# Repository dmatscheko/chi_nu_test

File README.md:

# χ_ν coherent-matter lift test

A pre-registered, falsifiable test of the OPH **χ_ν "coherent-matter lift"** claim
(the mechanism behind the OPH hoverboard concept), together with the audit work
that maps what the OPH corpus actually proves. The aim is to fix exactly what the
theory predicts **before** any data is taken, build the minimal self-reading device
the prediction requires, and let a pre-agreed decision rule, not either side's
prior, settle the outcome (detect / null / mundane / undefined).

Path shortcuts used throughout (`OPH:/`, `HOVER:/`, `ANS:/`) are defined in
Document A; `ANS:/` points at this repo's own [`communication/`](communication/)
directory.

## Layout

| Directory | What lives there |
|---|---|
| [`OPH_PROOF_CHAIN_HOLES.md`](OPH_PROOF_CHAIN_HOLES.md) | **The adversarial audit companion, two passes**: an independent hole inventory of the chain's interpretation layer (first pass F1–F19 against v5; second pass F20–F29 + per-finding disposition audits against v6.1; both passes independently *confirm* the formal layer by environment-level axiom sweeps). v6.1 adopted the first pass; **v7 closed both passes' mathematics by theorem** (T27/T28/T29 + F20/F25/F26 closures) and swept the second pass's residue ledger; disposition tables in the proof chain's §11. |
| [`OPH_PROOF_CHAIN_PAPER.md`](OPH_PROOF_CHAIN_PAPER.md) | **The expository paper**: the whole machine-checked proof chain written as ordinary mathematics: statement, proof, "why", and a plain-language paragraph per result. Adds nothing to the Lean tree (the tree is the authority); exists so a physicist can read the chain end-to-end without opening a `.lean` file. |
| [`test/`](test/) | **The physics test**: the pre-registration ledgers that govern the experiment. |
| [`proof_chain/`](proof_chain/) | **The minimal-proof-chain work**: what the OPH corpus proves (incl. the `formal/` Lean project that machine-checks it), the audit exchange with the OPH side, and the satellite-repo audits. |
| [`build/`](build/README.md) | **The hardware**: Milestone-1 self-reading piezo PoC (build plan, rev-2 electronics + schematics, jig, firmware) and the Stage-0 calibration results. |
| [`communication/`](communication/) | **The Q&A with the OPH side** (`ANS:/`): questions, replies, and the OPH-side PDFs. Absorbed from the former sibling repo on 2026-07-06. |

## The physics test (`test/`)

| File | Role |
|---|---|
| [`DOCUMENT_A_prediction_ledger.md`](test/DOCUMENT_A_prediction_ledger.md) | **Start here.** Imports the OPH math with verified provenance, records the agreed OPH-side inputs, discloses the conservation-law priors, and derives the falsifiable predictions + decision rule. Governs the outcome on its own. |
| [`DOCUMENT_C_run_matrix_and_error_budget.md`](test/DOCUMENT_C_run_matrix_and_error_budget.md) | The instrument, the run matrix (R-pre, ABBA, ACTIVE±/SHAM, blind controls), the error budget that fixes the detection floor, and the energy-budget logging. |
| [`DOCUMENT_B_critique_ledger.md`](test/DOCUMENT_B_critique_ledger.md) | Open-questions & credit ledger. Two live items, the ΔS-estimator bridge (G9) and the energy ledger (G10), plus the disposition of the original critique (mostly closed) and what stands regardless of any outcome. |

## The minimal proof chain (`proof_chain/`)

| File | Role |
|---|---|
| [`OPH_CORE_MINIMAL_PROOF_CHAIN.md`](proof_chain/OPH_CORE_MINIMAL_PROOF_CHAIN.md) | **v7.** The minimal proof chain for the core OPH idea: machine-checked (Lean) → paper-side theorems → conditional → asserted/calibrated, with the conservation-law bounds on the χ_ν chain. Background for all three ledgers. |
| [`formal/`](proof_chain/formal/) | **The Lean 4 project that machine-checks the chain**: 38 modules; 1284 non-internal theorem/def declarations swept at the environment level (v10 filter; earlier counts used a wider filter), 0 `sorry`, 0 custom axioms (incl. an attributed copy of the OPH core with its three `sorry`s discharged; the v7 modules closing the adversarial audit's mathematics; the v9 worldline/crawl theorems T36/T37; and the v10 campaign T38–T41: the parity splitting, two-power universality, the lone diagonal observer). See its [`README`](proof_chain/formal/README.md) and the statement-by-statement audit in [`RESULTS.md`](proof_chain/formal/RESULTS.md). |
| [`AUDIT_RESPONSE.md`](proof_chain/AUDIT_RESPONSE.md) | The OPH side's 2026-07-06 response to our audit: validity grading per gap + the July paper pass that answers it. |
| [`AUDIT_RESPONSE_REVIEW.md`](proof_chain/AUDIT_RESPONSE_REVIEW.md) | Our verification of that response: all pin-cites checked, the P-derivation code executed (two-P finding), three refinements (R1 feed-forward carrier, R2 falsifiers ≠ energy ledger, §P). |
| [`formal_audits/`](proof_chain/formal_audits/) | Raw audits of the `dula/` satellite repos (verdict: not proof-chain-relevant; one reusable artifact, ported). |

## How it fits together

**test/A**: what the theory predicts and how the result is decided ·
**test/C**: how it is measured · **test/B**: what stays open and what stands ·
**proof_chain/**: the standing of every imported claim and the audit exchange ·
**build/**: the device that produces the self-read receipt A requires ·
**communication/**: the primary-source Q&A the ledgers cite as `ANS:/`.

Version history lives in git: v0.1 ledgers (2026-06-02/03), the correction
pass ("corrections pass 1"), the v0.2 rewrite (2026-07-05), the audit exchange
and proof-chain v2 (2026-07-06), the v3/v4 `formal/` campaigns (the whole
chain machine-proven in one tree, 2026-07-06), the v5 campaign closing
the remaining open mathematics, incl. the D3 finite modular core and one
ledger erratum (2026-07-07), the v6 campaign settling the stride
conjecture (T25, the coprimality classification of two-column screens,
with the mirror lemma and the quotient lift as new tools) plus the
expository paper `OPH_PROOF_CHAIN_PAPER.md`, audited against the Lean tree,
and the v6.1 response to the adversarial audit `OPH_PROOF_CHAIN_HOLES.md`
(T26, the cosmological-constant step; the G10 pricing convention named;
the F18 erratum table applied; disposition in the proof chain's §11)
(2026-07-07), and the v7 campaign closing both audit passes' mathematics
by theorem (T27 Route A assembled; T28 the real-time modular flow; T29 the
channel bridge; the F20/F25/F26 closures; the ℤ₆ group isomorphism; the
theorem-grade energy anchors; the F22 evidence artifacts; the F21 residue
sweep) (2026-07-07). The former
`communication/` sibling repo's own history is at
https://github.com/dmatscheko/hoverboard-experimental-precursor.

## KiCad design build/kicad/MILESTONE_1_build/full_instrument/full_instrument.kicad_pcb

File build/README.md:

# Milestone 1 — Self-Reading Piezo PoC (build)

Hardware for **Milestone 1** of the χ_ν lift test: a small, self-contained object
that drives its own piezo rings, senses the response, and logs a reproducible
**coupling matrix** — the OPH "self-read receipt." No weighing and no lift claim
yet; this stage only proves that the self-reading object the experiment depends on
actually exists. Scope and decision rules live in
[`../test/DOCUMENT_A_prediction_ledger.md`](../test/DOCUMENT_A_prediction_ledger.md).

## Files

| File | What it is |
|---|---|
| [`MILESTONE_1_build.md`](MILESTONE_1_build.md) | The staged build plan — Stage 0 (characterise the rings on the Rigol) → Stage 1 (ESP32 logs the coupling matrix to Home Assistant). **Start here.** |
| [`electronics.md`](electronics.md) | Every subsystem as a chapter, each opening with a schematic: characterize the rings (Stage 0), system overview, controller/power/I²C, drive stage, ×120 amp + peak detector, TX select. **Rev 2 (2026-07-05):** real XIAO-C6 pinout, single 3.3 V rail, amplified RX chain, reset-after-burst capture — see the rev-2 notes in each chapter. |
| [`STAGE0_results_run1.md`](STAGE0_results_run1.md) | Lab-notebook record of the Stage-0 bench measurements (resonance, Q, coupling matrix, ring-2 finding). Versioned per run — copy to `…_run2.md` to repeat. |
| [`milestone1_jig.scad`](milestone1_jig.scad) | Parametric OpenSCAD carrier/ring jig — nonmagnetic, fixed ring spacing. |
| [`chi_nu_poc.yaml`](chi_nu_poc.yaml) | ESPHome firmware — drives the rings and publishes the timestamped C_ij matrix (+ shuffled control). |
| [`schematic/`](schematic/README.md) | Schematic sources (`*.sch`) and the generator that builds the `*.svg` diagrams embedded in `electronics.md`. |

## Regenerate the diagrams

```sh
cd schematic && make        # rebuild ../*.svg from the .sch sources
```

The `.sch` files are the source of truth; the `*.svg` are build artifacts.

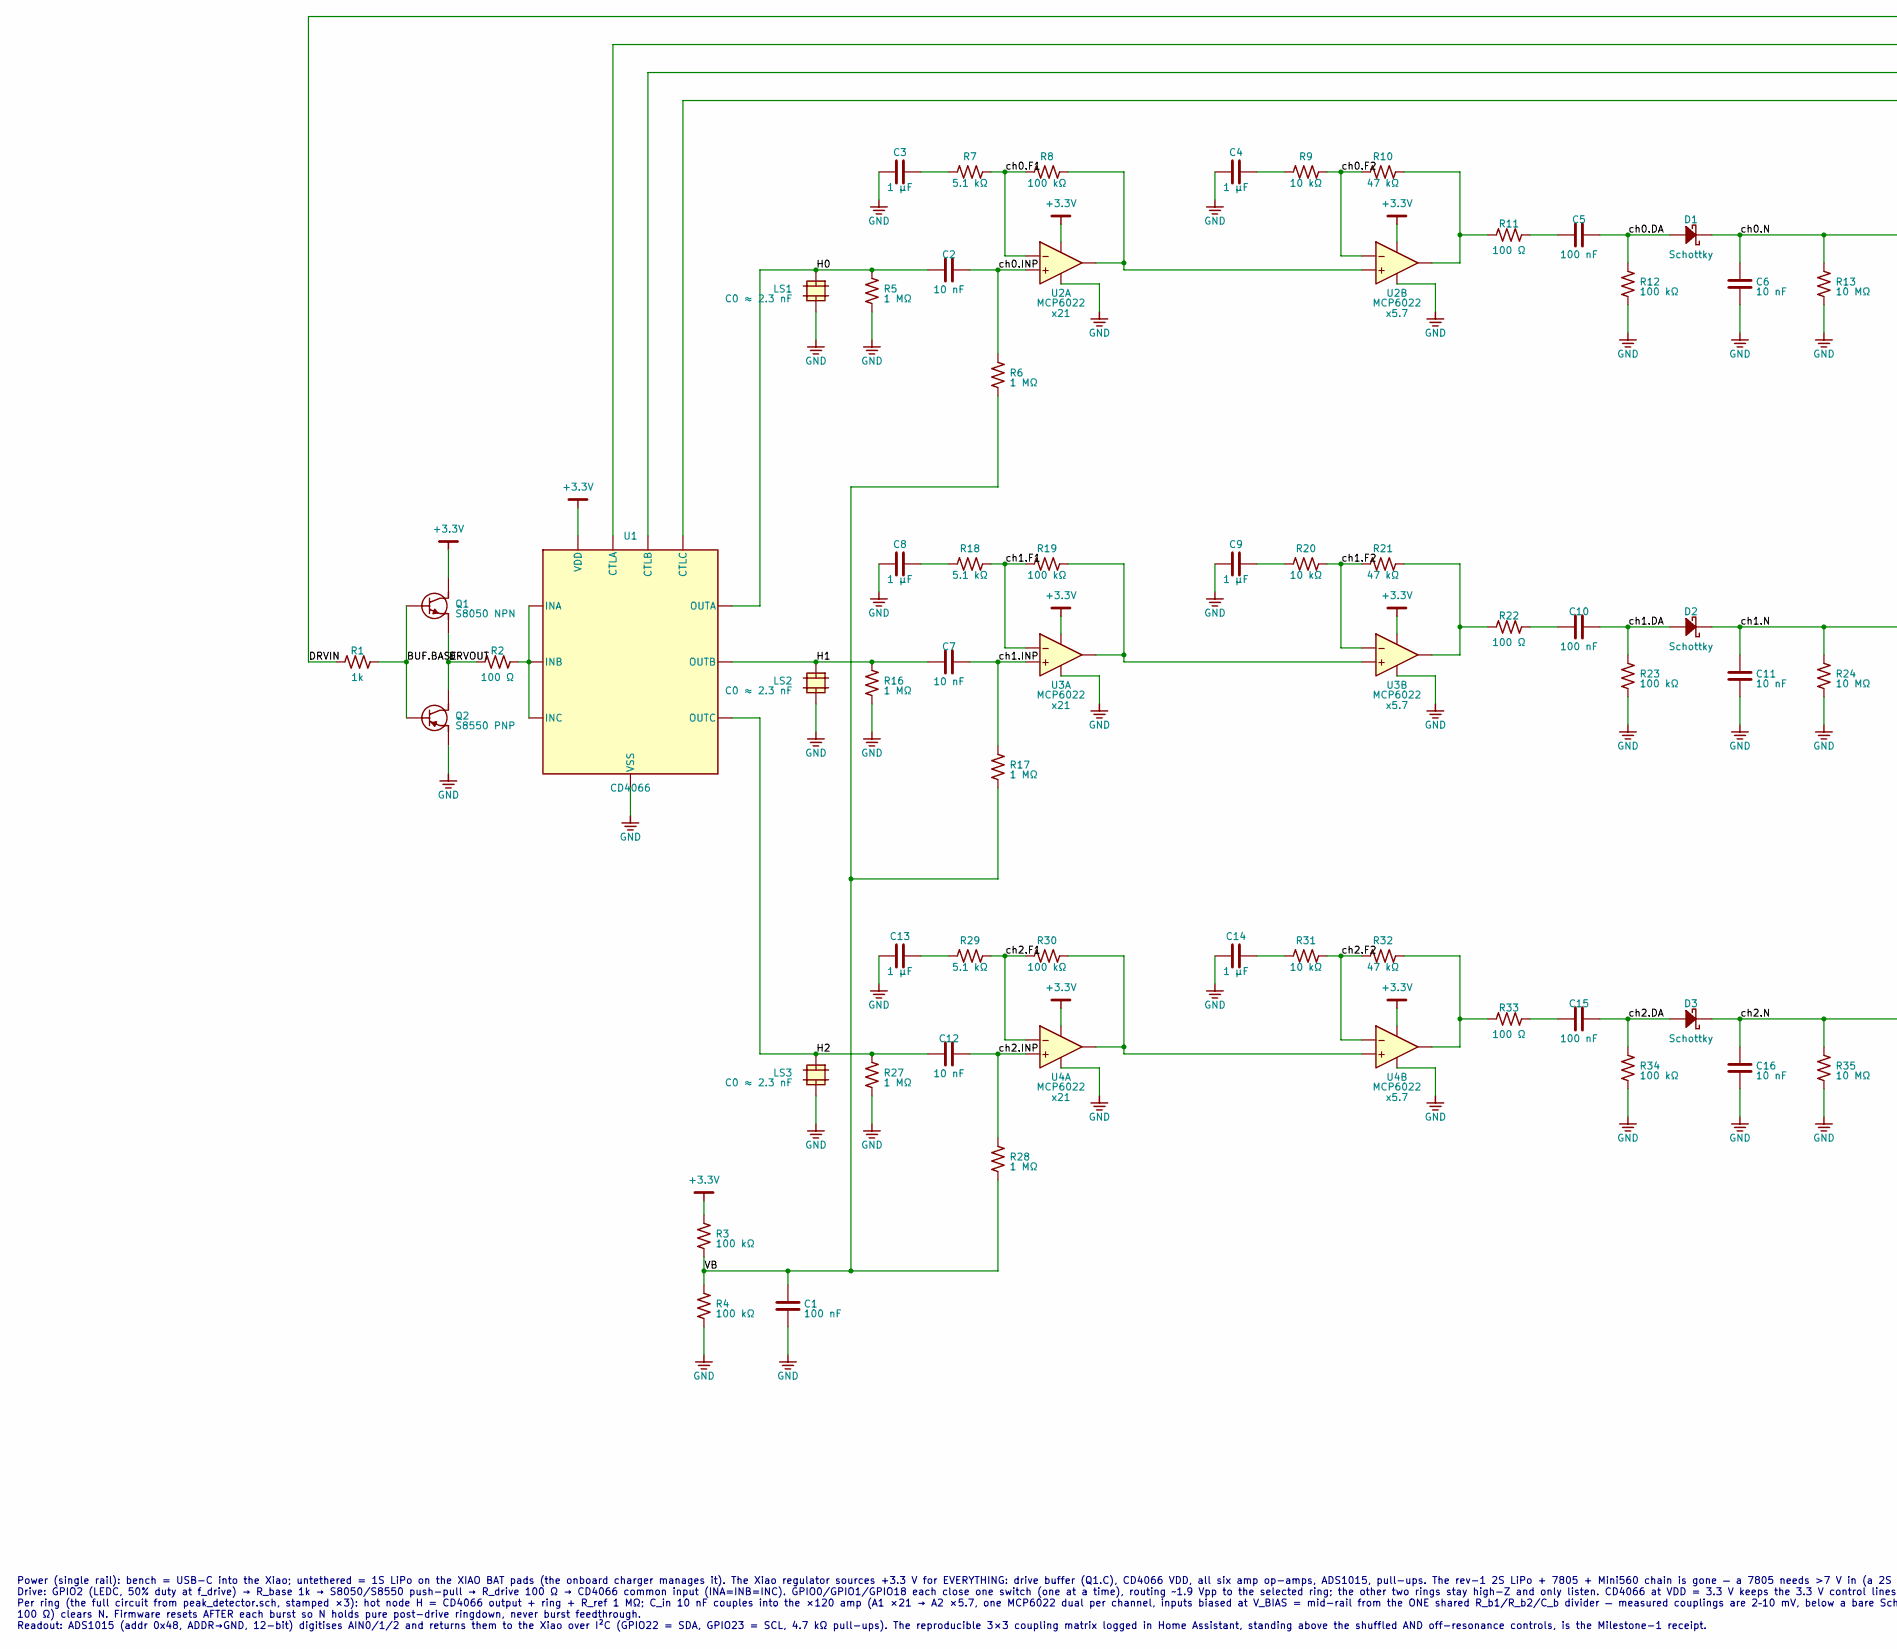
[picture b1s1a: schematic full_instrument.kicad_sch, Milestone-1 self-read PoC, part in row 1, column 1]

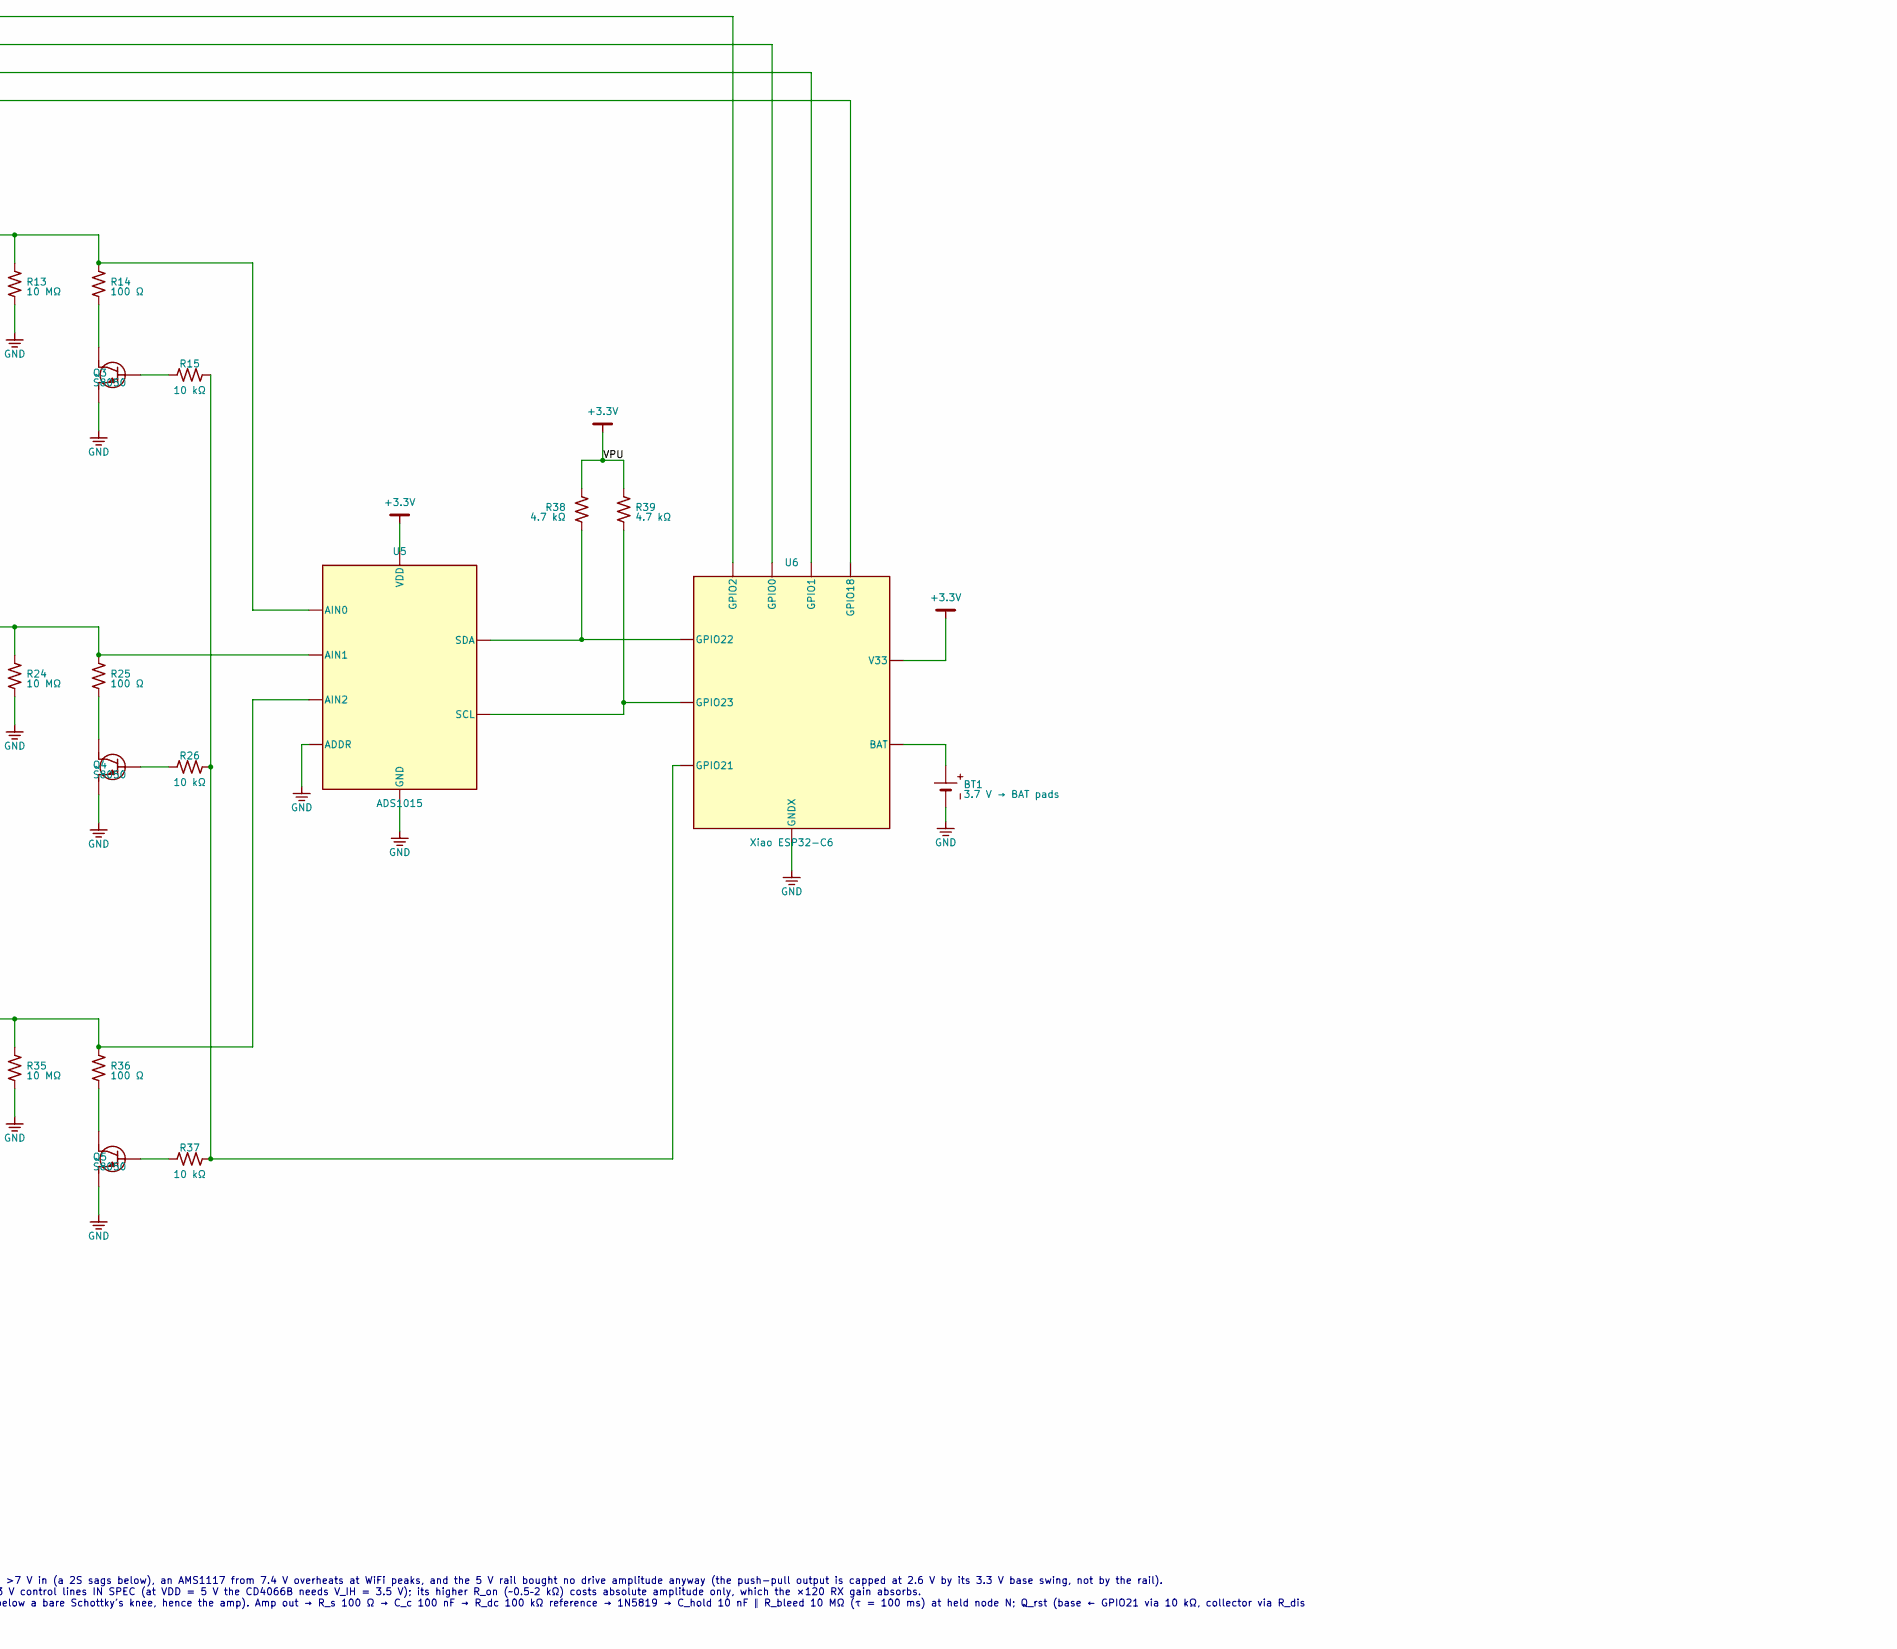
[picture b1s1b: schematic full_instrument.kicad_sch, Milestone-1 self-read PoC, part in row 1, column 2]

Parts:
BT1: 3.7 V → BAT pads; BatteryHolder_MPD_BH-18650-PC
C1, C5, C10, C15: 100 nF; C_1206_3216Metric
C2, C6, C7, C11, C12, C16: 10 nF; C_1206_3216Metric
C3, C4, C8, C9, C13, C14: 1 µF; C_1206_3216Metric
D1, D2, D3: Schottky; D_1206_3216Metric
LS1, LS2, LS3: C0 ≈ 2.3 nF; JST_PH_B2B-PH-K_1x02_P2.00mm_Vertical
Q1: S8050 NPN; SOT-23
Q2: S8550 PNP; SOT-23
Q3, Q4, Q5: S8050; SOT-23
R1: 1k; R_1206_3216Metric
R2, R11, R14, R22, R25, R33, R36: 100 Ω; R_1206_3216Metric
R3, R4, R8, R12, R19, R23, R30, R34: 100 kΩ; R_1206_3216Metric
R5, R6, R16, R17, R27, R28: 1 MΩ; R_1206_3216Metric
R7, R18, R29: 5.1 kΩ; R_1206_3216Metric
R9, R15, R20, R26, R31, R37: 10 kΩ; R_1206_3216Metric
R10, R21, R32: 47 kΩ; R_1206_3216Metric
R13, R24, R35: 10 MΩ; R_1206_3216Metric
R38, R39: 4.7 kΩ; R_1206_3216Metric
U1: CD4066; SOIC-14_3.9x8.7mm_P1.27mm
U2, U3, U4: MCP6022; SOIC-8_3.9x4.9mm_P1.27mm
U5: ADS1015; TSSOP-10_3x3mm_P0.5mm
U6: Xiao ESP32-C6; XIAO-ESP32-C6-SMD

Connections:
+3.3V: Q1.2 (C), R3.1 (a), R38.1 (a), R39.1 (a), U1.14 (VDD), U2.8 (V+), U3.8 (V+), U4.8 (V+), U5.8 (VDD), U6.12 (V33)
/BUF.BASE: Q1.1 (B), Q2.1 (B), R1.2 (b)
/DRVIN: R1.1 (a), U6.3 (GPIO2)
/DRVOUT: Q1.3 (E), Q2.3 (E), R2.1 (a)
/H0: C2.1 (a), LS1.1 (a), R5.1 (a), U1.2 (OUTA)
/H1: C7.1 (a), LS2.1 (a), R16.1 (a), U1.4 (OUTB)
/H2: C12.1 (a), LS3.1 (a), R27.1 (a), U1.9 (OUTC)
/VB: C1.1 (a), R3.2 (b), R4.1 (a), R6.2 (b), R17.2 (b), R28.2 (b)
/ch0.DA: C5.2 (b), D1.2 (A), R12.1 (a)
/ch0.F1: R7.1 (a), R8.2 (b), U2.2 (-)
/ch0.F2: R9.1 (a), R10.2 (b), U2.6 (-)
/ch0.INP: C2.2 (b), R6.1 (a), U2.3 (+)
/ch0.N: C6.1 (a), D1.1 (K), R13.1 (a), R14.1 (a), U5.4 (AIN0)
/ch1.DA: C10.2 (b), D2.2 (A), R23.1 (a)
/ch1.F1: R18.1 (a), R19.2 (b), U3.2 (-)
/ch1.F2: R20.1 (a), R21.2 (b), U3.6 (-)
/ch1.INP: C7.2 (b), R17.1 (a), U3.3 (+)
/ch1.N: C11.1 (a), D2.1 (K), R24.1 (a), R25.1 (a), U5.5 (AIN1)
/ch2.DA: C15.2 (b), D3.2 (A), R34.1 (a)
/ch2.F1: R29.1 (a), R30.2 (b), U4.2 (-)
/ch2.F2: R31.1 (a), R32.2 (b), U4.6 (-)
/ch2.INP: C12.2 (b), R28.1 (a), U4.3 (+)
/ch2.N: C16.1 (a), D3.1 (K), R35.1 (a), R36.1 (a), U5.6 (AIN2)
GND: BT1.2 (-), C1.2 (b), C3.2 (b), C4.2 (b), C6.2 (b), C8.2 (b), C9.2 (b), C11.2 (b), C13.2 (b), C14.2 (b), C16.2 (b), LS1.2 (b), LS2.2 (b), LS3.2 (b), Q2.2 (C), Q3.3 (E), Q4.3 (E), Q5.3 (E), R4.2 (b), R5.2 (b), R12.2 (b), R13.2 (b), R16.2 (b), R23.2 (b), R24.2 (b), R27.2 (b), R34.2 (b), R35.2 (b), U1.7 (VSS), U2.4 (V-), U3.4 (V-), U4.4 (V-), U5.1 (ADDR), U5.3 (GND), U6.13 (GNDX)
unnamed: BT1.1 (+), U6.23 (BAT)
unnamed: C3.1 (a), R7.2 (b)
unnamed: C4.1 (a), R9.2 (b)
unnamed: C5.1 (a), R11.2 (b)
unnamed: C8.1 (a), R18.2 (b)
unnamed: C9.1 (a), R20.2 (b)
unnamed: C10.1 (a), R22.2 (b)
unnamed: C13.1 (a), R29.2 (b)
unnamed: C14.1 (a), R31.2 (b)
unnamed: C15.1 (a), R33.2 (b)
unnamed: Q3.1 (B), R15.1 (a)
unnamed: Q3.2 (C), R14.2 (b)
unnamed: Q4.1 (B), R26.1 (a)
unnamed: Q4.2 (C), R25.2 (b)
unnamed: Q5.1 (B), R37.1 (a)
unnamed: Q5.2 (C), R36.2 (b)
unnamed: R2.2 (b), U1.1 (INA), U1.3 (INB), U1.8 (INC)
unnamed: R8.1 (a), U2.1 (out), U2.5 (+)
unnamed: R10.1 (a), R11.1 (a), U2.7 (out)
unnamed: R15.2 (b), R26.2 (b), R37.2 (b), U6.4 (GPIO21)
unnamed: R19.1 (a), U3.1 (out), U3.5 (+)
unnamed: R21.1 (a), R22.1 (a), U3.7 (out)
unnamed: R30.1 (a), U4.1 (out), U4.5 (+)
unnamed: R32.1 (a), R33.1 (a), U4.7 (out)
unnamed: R38.2 (b), U5.9 (SDA), U6.5 (GPIO22)
unnamed: R39.2 (b), U5.10 (SCL), U6.6 (GPIO23)
unnamed: U1.13 (CTLA), U6.1 (GPIO0)
unnamed: U1.5 (CTLB), U6.2 (GPIO1)
unnamed: U1.6 (CTLC), U6.11 (GPIO18)

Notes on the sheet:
Power (single rail): bench = USB-C into the Xiao; untethered = 1S LiPo on the XIAO BAT pads (the onboard charger manages it). The Xiao regulator sources +3.3 V for EVERYTHING: drive buffer (Q1.C), CD4066 VDD, all six amp op-amps, ADS1015, pull-ups. The rev-1 2S LiPo + 7805 + Mini560 chain is gone —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

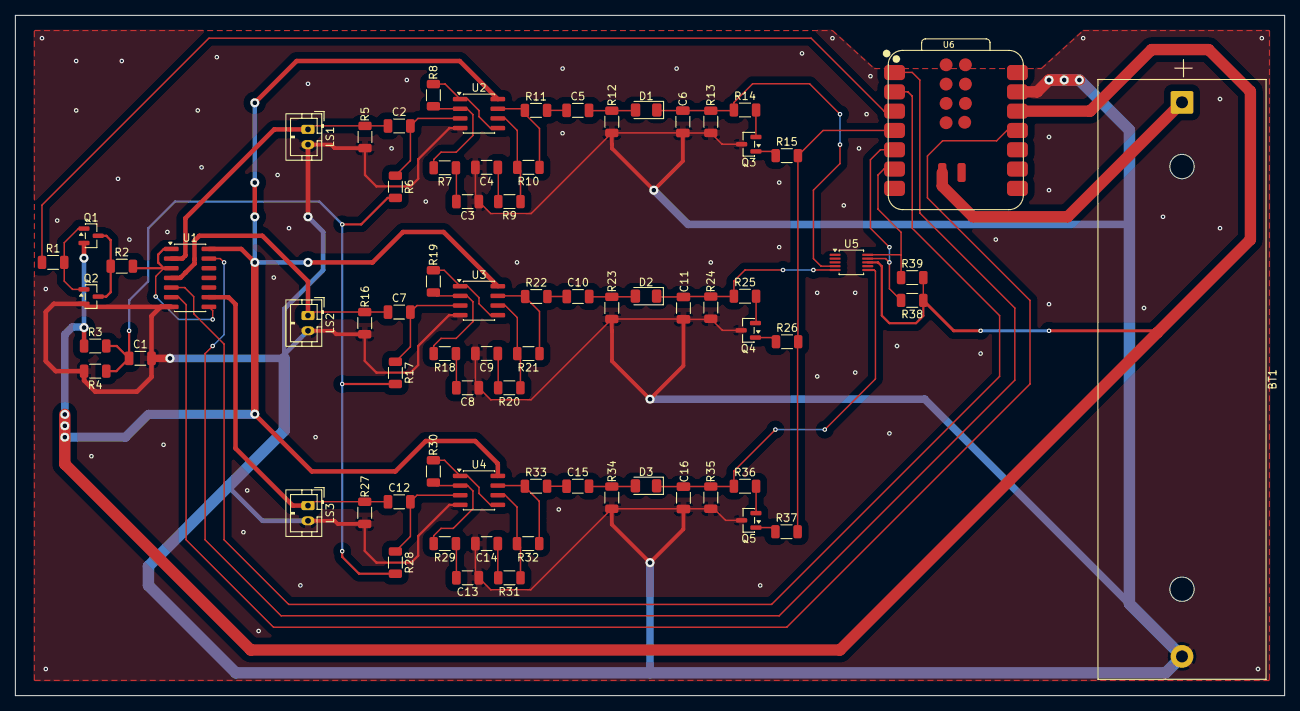
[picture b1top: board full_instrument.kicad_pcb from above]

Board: 4 copper layers, 167.0 x 89.5 mm, 73 parts (0 on the bottom side), 53 nets.
